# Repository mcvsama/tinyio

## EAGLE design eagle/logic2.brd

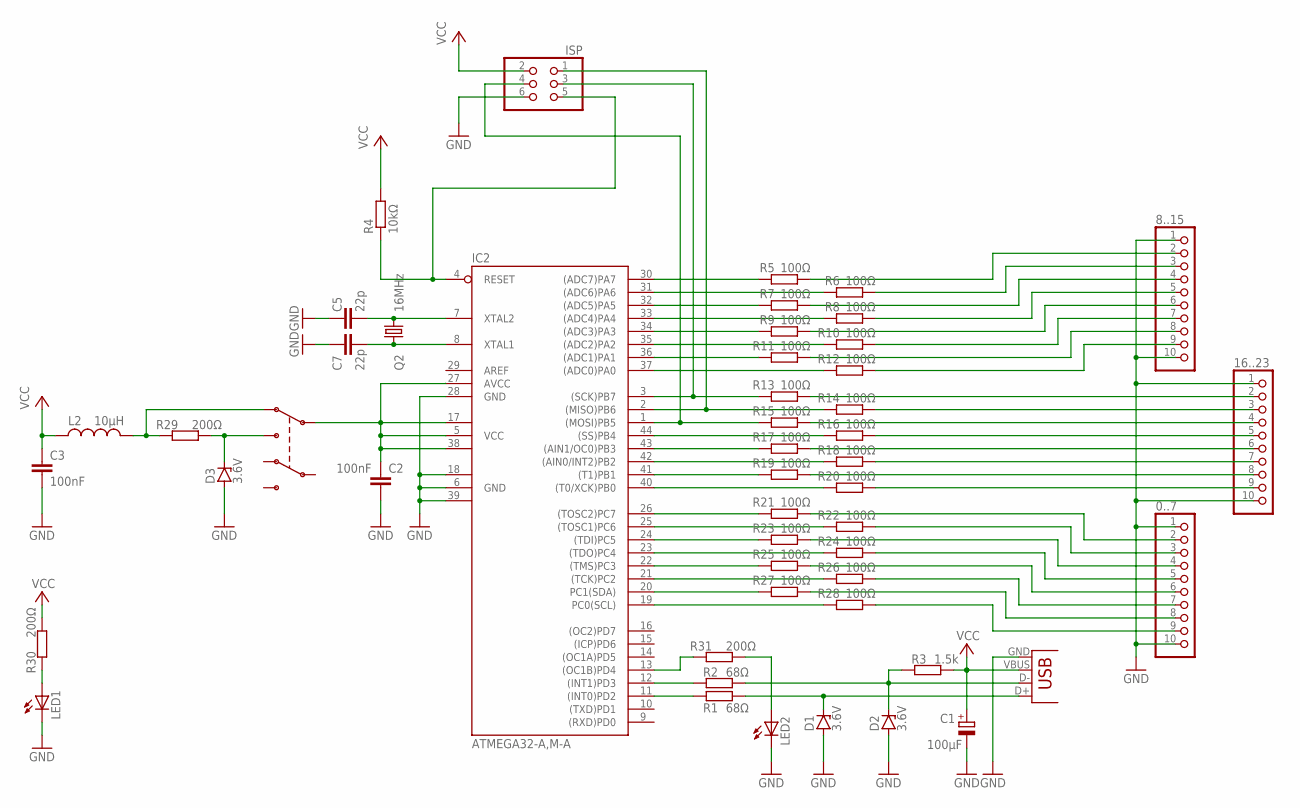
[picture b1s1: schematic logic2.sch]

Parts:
0..7, 8..15, 16..23: PINHD-1X10_2.54-SMD; 1X10SMD
C1: 100µF; D/7343-31R
C2, C3: 100nF; C1206
C5, C7: 22p; C1206
D1, D2, D3: 3.6V; DIODE-ZENER-0805
IC2: ATMEGA32-A,M-A; TQFP44
ISP: PINHD-2X3_2.54-SMD; 2X03SMD
L2: 10µH; L1812
LED1, LED2: LEDCHIPLED_0805; CHIPLED_0805
Q2: 16MHz; CSM-7X-DU
R1, R2: 68Ω; R1206
R3: 1.5k; R1206
R4: 10kΩ; R0603
R5, R6, R7, R8, R9, R10, R11, R12, R13, R14, R15, R16, R17, R18, R19, R20, R21, R22, R23, R24, R25, R26, R27, R28: 100Ω; R0603
R29, R30, R31: 200Ω; R1206
U$3: SWTICH-DPDT1; SWITCH-TOP-DPDT
X1: USBSMD; USB-MINIB

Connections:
GND: 0..7.1, 0..7.10, 8..15.1, 8..15.10, 16..23.1, 16..23.10, C1.-, C2.2, C3.2, C5.1, C7.1, D1.A, D2.A, D3.A, IC2.6 (GND), IC2.18 (GND1), IC2.28 (GND), IC2.39 (GND2), ISP.6, LED1.C, LED2.C, X1.GND
unnamed: IC2.12 ((INT1)PD3), R2.1
unnamed: IC2.11 ((INT0)PD2), R1.1
unnamed: D1.K (C), R1.2, X1.D+
unnamed: D2.K (C), R2.2, R3.1, X1.D-
unnamed: C2.1, IC2.5 (VCC), IC2.17 (VCC1), IC2.27 (AVCC), IC2.38 (VCC2), U$3.1
unnamed: IC2.4 (RESET), ISP.5, R4.1
unnamed: IC2.30 ((ADC7)PA7), R5.2
unnamed: IC2.31 ((ADC6)PA6), R6.2
unnamed: IC2.32 ((ADC5)PA5), R7.2
unnamed: IC2.33 ((ADC4)PA4), R8.2
unnamed: IC2.34 ((ADC3)PA3), R9.2
unnamed: LED1.A, R30.1
unnamed: C7.2, IC2.8 (XTAL1), Q2.1
unnamed: IC2.35 ((ADC2)PA2), R10.2
unnamed: IC2.36 ((ADC1)PA1), R11.2
unnamed: IC2.37 ((ADC0)PA0), R12.2
unnamed: IC2.3 ((SCK)PB7), ISP.3, R13.2
unnamed: IC2.2 ((MISO)PB6), ISP.1, R14.2
unnamed: IC2.44 ((SS)PB4), R16.2
unnamed: IC2.1 ((MOSI)PB5), ISP.4, R15.2
unnamed: IC2.43 ((AIN1/OC0)PB3), R17.2
unnamed: IC2.42 ((AIN0/INT2)PB2), R18.2
unnamed: IC2.40 ((T0/XCK)PB0), R20.2
unnamed: IC2.41 ((T1)PB1), R19.2
unnamed: IC2.26 ((TOSC2)PC7), R21.2
unnamed: IC2.25 ((TOSC1)PC6), R22.2
unnamed: IC2.23 ((TDO)PC4), R24.2
unnamed: IC2.21 ((TCK)PC2), R26.2
unnamed: IC2.19 (PC0(SCL)), R28.2
unnamed: IC2.24 ((TDI)PC5), R23.2
unnamed: IC2.22 ((TMS)PC3), R25.2
unnamed: IC2.20 (PC1(SDA)), R27.2
unnamed: 8..15.2, R5.1
unnamed: 8..15.3, R6.1
unnamed: 8..15.4, R7.1
unnamed: 8..15.5, R8.1
unnamed: 8..15.6, R9.1
unnamed: 8..15.7, R10.1
unnamed: 8..15.8, R11.1
unnamed: 8..15.9, R12.1
unnamed: 16..23.2, R13.1
unnamed: 16..23.3, R14.1
unnamed: 16..23.4, R15.1
unnamed: 16..23.5, R16.1
unnamed: 16..23.6, R17.1
unnamed: 16..23.7, R18.1
unnamed: 16..23.8, R19.1
unnamed: 16..23.9, R20.1
unnamed: 0..7.2, R21.1
unnamed: 0..7.3, R22.1
unnamed: 0..7.4, R23.1
unnamed: 0..7.5, R24.1
unnamed: 0..7.6, R25.1
unnamed: 0..7.7, R26.1
unnamed: 0..7.8, R27.1
unnamed: 0..7.9, R28.1
unnamed: D3.K (C), R29.2, U$3.1NO
unnamed: L2.1, R29.1, U$3.1NC
unnamed: C5.2, IC2.7 (XTAL2), Q2.2
unnamed: IC2.13 ((OC1B)PD4), R31.1
unnamed: LED2.A, R31.2
VCC: C1.+, C3.1, ISP.2, L2.2, R3.2, R4.2, R30.2, X1.VBUS

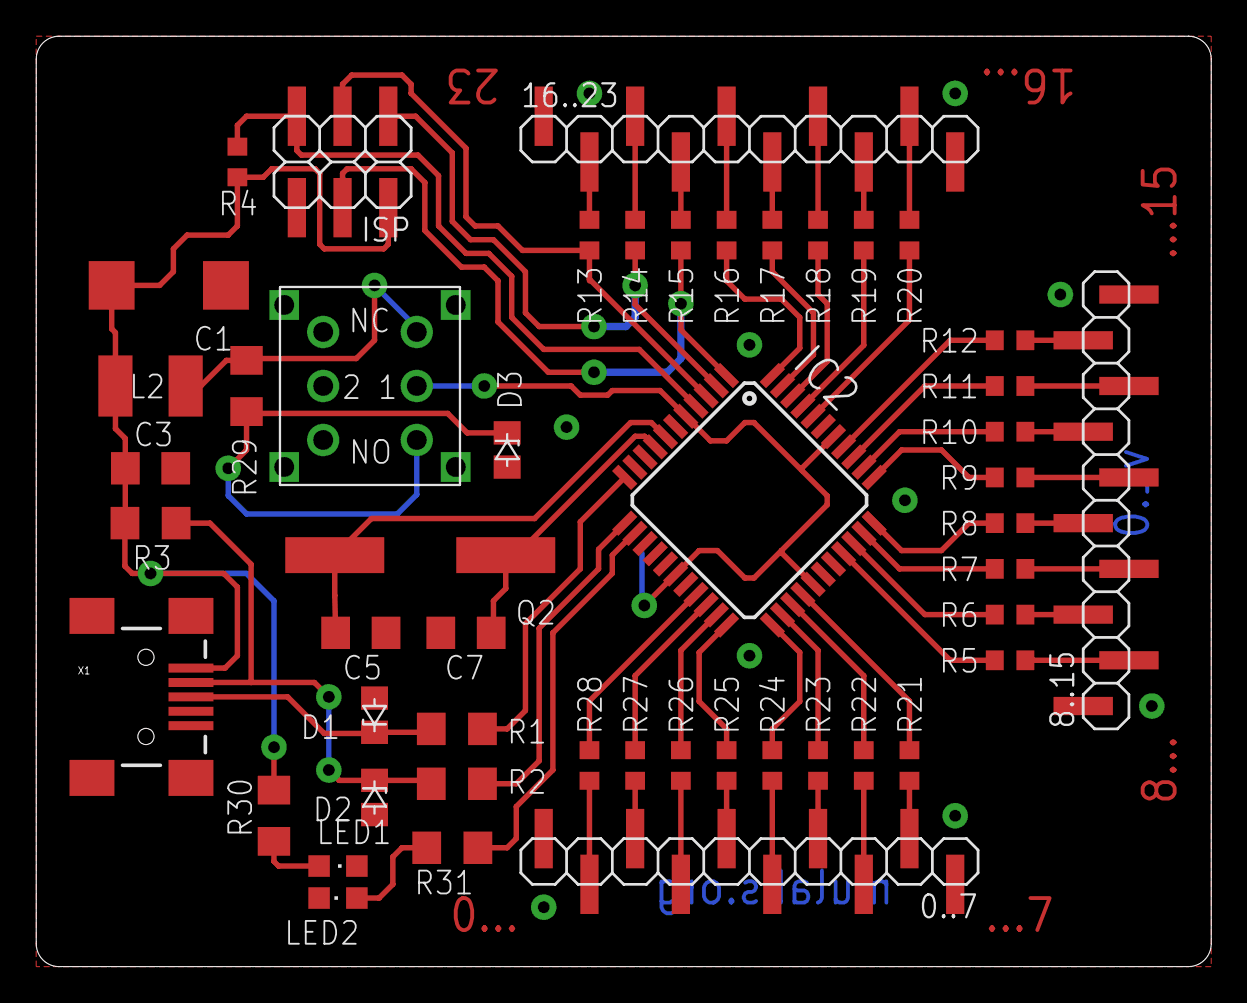
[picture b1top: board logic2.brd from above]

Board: 2 copper layers, 65.3 x 51.7 mm, 50 parts (1 on the bottom side), 63 nets.

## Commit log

2014-11-27 Import eagle project
2014-11-27 Import firmware and UDEV config file
2014-11-27 Import the software
2014-11-27 Add gitignores and some READMEs.
2014-11-27 Remove unused file
2014-11-27 Let my TinyIO have serial 00000001.
2014-11-27 Fix output port setting.
2014-11-27 WUT, Makefile.local is not supposed to be in repository.
2014-11-27 Add TinyIO abstraction/split TinyIO into manager, device and (open) interface.
2014-11-27 Update gui.cc, still just POC.
2014-11-28 Support reading of pins state.
2014-11-28 Serious thing renaming!
2014-11-29 Fix udev rules file.
2014-11-29 Use C++14.
2014-11-29 First GUI.
2014-11-30 More stubbing of the GUI.
2014-12-01 Add breaks lol.
2014-12-01 Implement switching logic levels and pin directions in GUI.
2014-12-01 Rename eagle files. Add PDF schematics.
2014-12-01 Support pull-ups. Nicer UI.
2014-12-02 Support reading actual pin directions.
2014-12-02 Fix blinking LED.
2014-12-02 Implement hold and disconnect functions.
2014-12-02 Ok, clearer ownership (parent QWidget when bare pointer).
2014-12-02 Increase sampling rate.
2014-12-02 Use instantly editable QLineEdit instead of QLabel.
2014-12-04 Allow auto-reconnecting to device after it's reconnected.
    Separate pins config into DeviceConfig.
    Find devices by serial number.
2014-12-17 Style.
2014-12-17 Update schematics PDF.
2014-12-23 Enable/disable widgets when device is online/offline.
2015-04-22 Button height fix.

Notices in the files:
parts and their libraries:
SparkFun: Licensing: CC v3.0 Share-Alike You are welcome to use this library for commercial purposes.
